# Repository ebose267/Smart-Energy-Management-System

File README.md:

# Smart-Energy-Management-System
An IoT-enabled, ESP32-powered Smart Energy Management System (SEMS) featuring high-precision AC power metering (PZEM-004T v3), zero-wear solid-state load switching, local color TFT visualization (ST7735), web-based dashboard management, and deterministic rule-based safety protection.
[github_readme_file.md](https://github.com/user-attachments/files/34116563/github_readme_file.md)
# IoT-Based Smart Energy Management System (SEMS)

An integrated, low-cost (~₦49,400) IoT smart energy meter and load controller engineered on the ESP32 platform. The system provides real-time single-phase AC electrical parameter measurement, local graphical display feedback via an ST7735 TFT screen, zero-wear load switching using a Solid-State Relay (SSR), embedded web dashboard monitoring, and local non-volatile credit tracking.

---

## 🌟 Key Features

* **High-Precision Multi-Parameter Sensing:** Real-time sampling of Root Mean Square (RMS) Voltage, RMS Current, Active Power ($P$), Apparent Power ($S$), Reactive Power ($Q$), Power Factor ($\text{PF}$), Line Frequency ($f$), and Energy Accumulation ($E_{\text{kWh}}$) using the PZEM-004T v3 metering IC.
* **Deterministic Rule-Based Protection Engine:**
  * **Voltage Guardrails:** Automated relay cut-off during brownouts ($V < 190\text{V}$) or over-voltage spikes ($V > 253\text{V}$).
  * **Overload Latching:** Immediate trip upon overcurrent ($I > 10\text{A}$) with a 30-second cooldown timer. Latches permanently if tripped 3 times in 10 minutes.
  * **Bypass / Energy Theft Detection:** Triggers an instant alert if load current ($I > 0.05\text{A}$) flows while the relay is driven `OFF`.
  * **Credit Limit Enforcement:** Automatic relay disconnection when credit balance reaches $\le \text{NGN } 0.00$, accompanied by a low-credit warning at $\le \text{NGN } 200.00$.
* **Zero-Wear Solid-State Switching:** Driven via a 25A AC Solid-State Relay (SSR) with zero-crossing switching logic, eliminating mechanical contact arcing and contact welding.
* **Dual-Domain Local & Cloud Visualization:**
  * **Local UI:** 1.8-inch ST7735 128x160 color TFT display driven via Hardware SPI.
  * **Embedded Web Server:** Hosts a local HTTP REST dashboard (`http://smartenergy.local`) for live monitoring, prepaid account recharge, parameter tuning, and relay manual override.
* **Persistent Non-Volatile Memory (NVS):** Synchronized saving of credit balance, energy indices, and parameter bounds via the ESP32 `Preferences` API to ensure resilience against sudden grid power failure.
* **Multi-Tier Network Resilience:** Auto-reconnects to local Wi-Fi router; automatically spins up a fallback Access Point (`SmartEnergy-Setup`) if router connectivity is unavailable.

---

## 📌 Hardware Pinout Connections

The ESP32 microcontroller coordinates peripherals using hardware UART2, SPI, and dedicated GPIO lines:

| Subsystem / Module | Module Pin | ESP32 GPIO Pin | Protocol / Signal Type |
| :--- | :--- | :--- | :--- |
| **PZEM-004T v3 Meter** | TX Pin | **GPIO 16** (RX2) | Hardware UART2 Receive (3.3V TTL) |
| **PZEM-004T v3 Meter** | RX Pin | **GPIO 17** (TX2) | Hardware UART2 Transmit (3.3V TTL) |
| **ST7735 TFT Display** | CS (Chip Select) | **GPIO 5** | Hardware SPI Output |
| **ST7735 TFT Display** | SCLK (Clock) | **GPIO 18** | Hardware SPI Output |
| **ST7735 TFT Display** | DC (Data/Command) | **GPIO 21** | Hardware SPI Output |
| **ST7735 TFT Display** | RST (Reset) | **GPIO 22** | Hardware SPI Output |
| **ST7735 TFT Display** | MOSI (Master Out) | **GPIO 23** | Hardware SPI Output |
| **Solid-State Relay (SSR)**| Control Signal | **GPIO 4** | Digital Output (Active-LOW) |
| **Manual Override Button** | Switch Input | **GPIO 32** | Digital Input (Internal Pull-Up) |

> ⚠️ **Critical Safety Wiring Note:** The PZEM-004T voltage sensing taps and split-core Current Transformer (CT) clamp **MUST** be connected on the *supply side* (upstream) of the relay contacts. This enables continuous grid voltage sampling while the relay is open, allowing grid stability verification before energizing loads and enabling bypass/theft detection.

---

## 📐 Circuit Architecture & System Analysis

### Single-Phase AC Formulas
* **RMS Calculations:**
  $$V_{\text{RMS}} = \sqrt{\frac{1}{N} \sum_{i=1}^{N} v_i^2}, \quad I_{\text{RMS}} = \sqrt{\frac{1}{N} \sum_{i=1}^{N} i_i^2}$$
* **Power Quantities:**
  $$\text{Apparent Power } (S) = V_{\text{RMS}} \times I_{\text{RMS}} \quad [\text{VA}]$$
  $$\text{Active Power } (P) = V_{\text{RMS}} \times I_{\text{RMS}} \times \cos\phi \quad [\text{W}]$$
  $$\text{Reactive Power } (Q) = \sqrt{S^2 - P^2} \quad [\text{VAR}]$$
* **Discrete Energy Accumulation:**
  $$E_{\text{kWh}} = \frac{\sum (P_i \times \Delta t)}{3,600,000}$$
  *(Where $P_i$ is active power in Watts, and $\Delta t$ is the sampling interval in seconds).*

---

## 🛠️ Software Installation & Flashing Guide

### 1. Prerequisites & Dependencies
Install the [Arduino IDE](https://www.arduino.cc/en/software) (v2.0+) and add the ESP32 board manager URL (`https://dl.espressif.com/dl/package_esp32_index.json`).

Install the following libraries via the Arduino Library Manager:
* `PZEM004Tv30` (by Jakub Mandula)
* `Adafruit GFX Library` (by Adafruit)
* `Adafruit ST7735 and ST7789 Library` (by Adafruit)
* Built-in ESP32 core libraries (`WiFi`, `WebServer`, `ESPmDNS`, `Preferences`, `SPI`)

### 2. Flashing Procedure
1. Clone this repository:
   ```bash
   git clone https://github.com/YOUR-USERNAME/smart-energy-management-system.git
   ```
2. Open `firmware/SmartEnergySystem.ino` in Arduino IDE.
3. Select your ESP32 board target: **Tools -> Board -> ESP32 Arduino -> ESP32 Dev Module**.
4. Configure Wi-Fi credentials inside `SmartEnergySystem.ino`:
   ```cpp
   const char* WIFI_SSID = "YOUR_WIFI_SSID";
   const char* WIFI_PASS = "YOUR_WIFI_PASSWORD";
   ```
5. Connect your ESP32 via Micro-USB/USB-C, select the correct COM port, and click **Upload**.

---

## 🌐 Web Dashboard Endpoints

When connected to Wi-Fi, navigate to `http://smartenergy.local` or the assigned IP address:

| REST Endpoint | HTTP Method | Description |
| :--- | :--- | :--- |
| `/` | `GET` | Renders the primary live monitoring dashboard (HTML/JS). |
| `/login` | `GET / POST` | User session authentication handler. |
| `/data` | `GET` | Returns live JSON telemetry (Voltage, Current, Power, Energy, Balance). |
| `/recharge` | `POST` | Processes credit top-up requests (`amount`). |
| `/setRelay` | `POST` | Toggles relay position manually (`state=1` or `state=0`). |
| `/settings` | `POST` | Updates system voltage/current protection boundaries and tariffs. |
| `/password` | `POST` | Updates admin access credentials. |
| `/factoryReset` | `POST` | Erases NVS memory and restores default factory parameters. |

---

## 💰 Bill of Engineering Measurement and Evaluation (BEME)

| S/N | Material / Component Description | Quantity | Unit Cost (₦) | Total Cost (₦) |
| :---: | :--- | :---: | :---: | :---: |
| 1 | ESP32 Dev Module Microcontroller | 1 | 10,000 | 10,000 |
| 2 | PZEM-004T v3 Energy Metering Module + CT Clamp | 1 | 15,000 | 15,000 |
| 3 | LM2596 DC-DC Buck Converter Module | 1 | 6,000 | 6,000 |
| 4 | 1.8-inch ST7735 Color TFT Display Module | 1 | 5,500 | 5,500 |
| 5 | 3.7V Lithium-Ion Battery (3000mAh) | 2 | 1,500 | 3,000 |
| 6 | Perforated Circuit Board (5x7 cm Perfboard) | 1 | 1,500 | 1,500 |
| 7 | Female / Male Header Pin Strips Set | 1 Pack | 1,200 | 1,200 |
| 8 | Solid-State Relay (SSR 25A 24-380V AC) | 1 | 1,200 | 1,200 |
| 9 | Tactile Override Switch / Power Pushbutton | 1 | 500 | 500 |
| 10 | System Project Protective Enclosure Casing | 1 | 4,000 | 4,000 |
| 11 | Assembly Fasteners & Adhesive Glue | 1 Set | 1,500 | 1,500 |
| **TOTAL** | **BILL OF ENGINEERING MEASUREMENT & EVALUATION** | - | - | **₦49,400** |

---

## 📁 Repository Structure

```text
smart-energy-management-system/
├── firmware/
│   └── SmartEnergySystem.ino       # ESP32 Production C++ Firmware
├── hardware/
│   ├── schematics/                 # Schematic Diagram Files (.PDF / .KiCAD)
│   ├── pcb/                        # Dual-Layer PCB Gerber Fabrication Files
│   └── enclosure/                  # 3D CAD Enclosure Models (.STL / .STEP)
├── docs/
│   └── SEMS_Project_Documentation.docx  # Full Audited Technical Documentation
├── media/
│   ├── block_diagram.png           # Hardware Architecture Diagram
│   └── prototype_photo.jpg         # Assembled Hardware Prototype Image
├── .gitignore
├── LICENSE                         # Open-Source MIT License
└── README.md                       # Repository Overview Document
```

---

## 📜 License

This project is licensed under the MIT License - see the [LICENSE](LICENSE) file for details.

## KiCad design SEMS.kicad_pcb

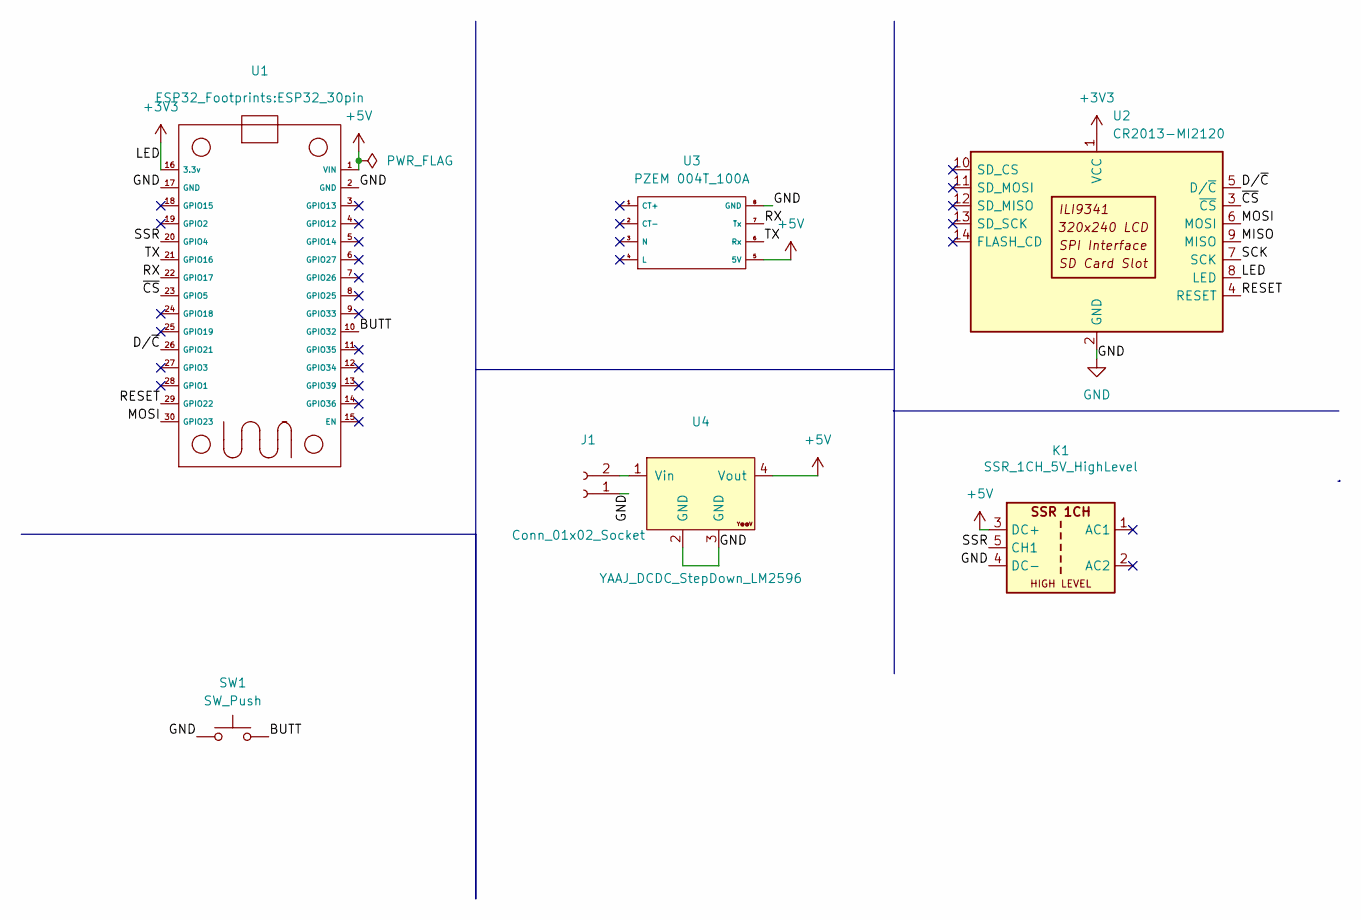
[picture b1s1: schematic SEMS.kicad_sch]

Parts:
J1: Conn_01x02_Socket; B2B-PH-SM4-TB
K1: SSR_1CH_5V_HighLevel; SSR_Module_1CH_HighLevel_G3MB202P-1
SW1: SW_Push; SW_TH_Tactile_Omron_B3F-10xx
U1: ESP32_30pin
U2: CR2013-MI2120
U3: PZEM 004T_100A; PZEM-004
U4: YAAJ_DCDC_StepDown_LM2596

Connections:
+3V3: U1.16 (3.3v), U2.1 (VCC), U2.8 (LED)
+5V: K1.3 (DC+), U1.1 (VIN), U3.5 (5V), U4.4 (Vout)
/BUTT: SW1.2, U1.10 (GPIO32)
/D/~C: U1.26 (GPIO21), U2.5 (D/~C)
/MISO: U2.9 (MISO)
/MOSI: U1.30 (GPIO23), U2.6 (MOSI)
/RESET: U1.29 (GPIO22), U2.4 (RESET)
/RX: U1.22 (GPIO17), U3.7 (Tx)
/SCK: U2.7 (SCK)
/SSR: K1.5 (CH1), U1.20 (GPIO4)
/TX: U1.21 (GPIO16), U3.6 (Rx)
/~CS: U1.23 (GPIO5), U2.3 (~CS)
GND: J1.1, K1.4 (DC-), SW1.1, U1.2 (GND), U1.17 (GND), U2.2 (GND), U3.8 (GND), U4.2 (GND), U4.3 (GND)
unnamed: J1.2, U4.1 (Vin)

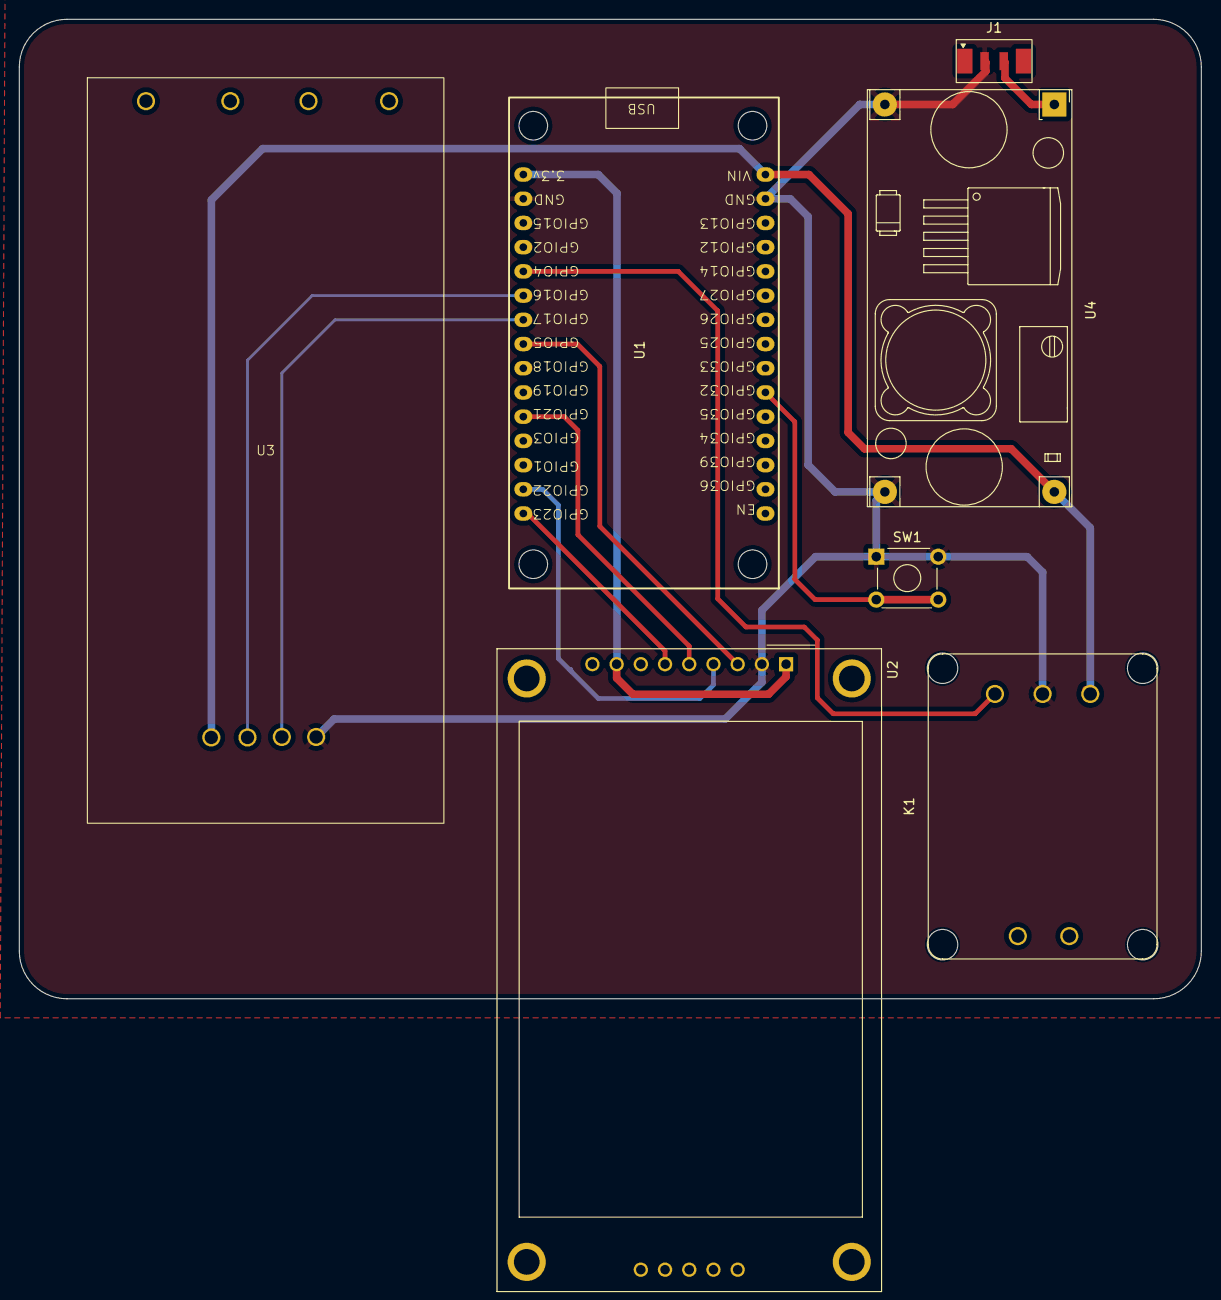
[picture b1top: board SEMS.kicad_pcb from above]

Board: 2 copper layers, 124.0 x 102.7 mm, 7 parts (0 on the bottom side), 12 nets.

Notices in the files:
README.md:
License: MIT
